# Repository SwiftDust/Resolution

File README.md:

## Resolution

In this repository, I am documenting my progress of learning two new skills: hardware design and CAD. I will hopefully use these in the future to make some really cool projects!

This is made possible by Hack Club's Resolution, a program for teenagers 13-18 years old to learn new skills and earn prizes.

### How it works

I am following the pathways "Hardware" and "Design". These are divided into different weeks: week 1-8. The pathways and weeks have their separate folders with a README to show what the projects are and how I did it, and the project files.

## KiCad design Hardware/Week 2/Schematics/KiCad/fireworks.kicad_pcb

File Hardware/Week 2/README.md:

# Fireworks

This is a fireworks PCB. I made this because starting 2026, fireworks are forbidden on New Years Eve in The Netherlands. Fireworks are always a huge tradition for my family and for our people in general, and I made a little 'fake' firework simulation to make up for it.

## Simulation

The LEDs are all connected to a 5V power source, which routes through 1k capacitors to the LEDs. Between the LEDs and the capacitors are transistors, whose outputs are fed into each other. In between the LEDs are capacitors, which constantly charge and discharge due to the constant change in voltage. This creates a sequencing effect in each of the LED series. They are connected in groups of three.

[Link to schematic](https://is.gd/zdDuyj)

## Schematic

## PCB

---

Much thanks to Rudy (@Outdatedcandy82), for staying super patient and helping me wherever he could!

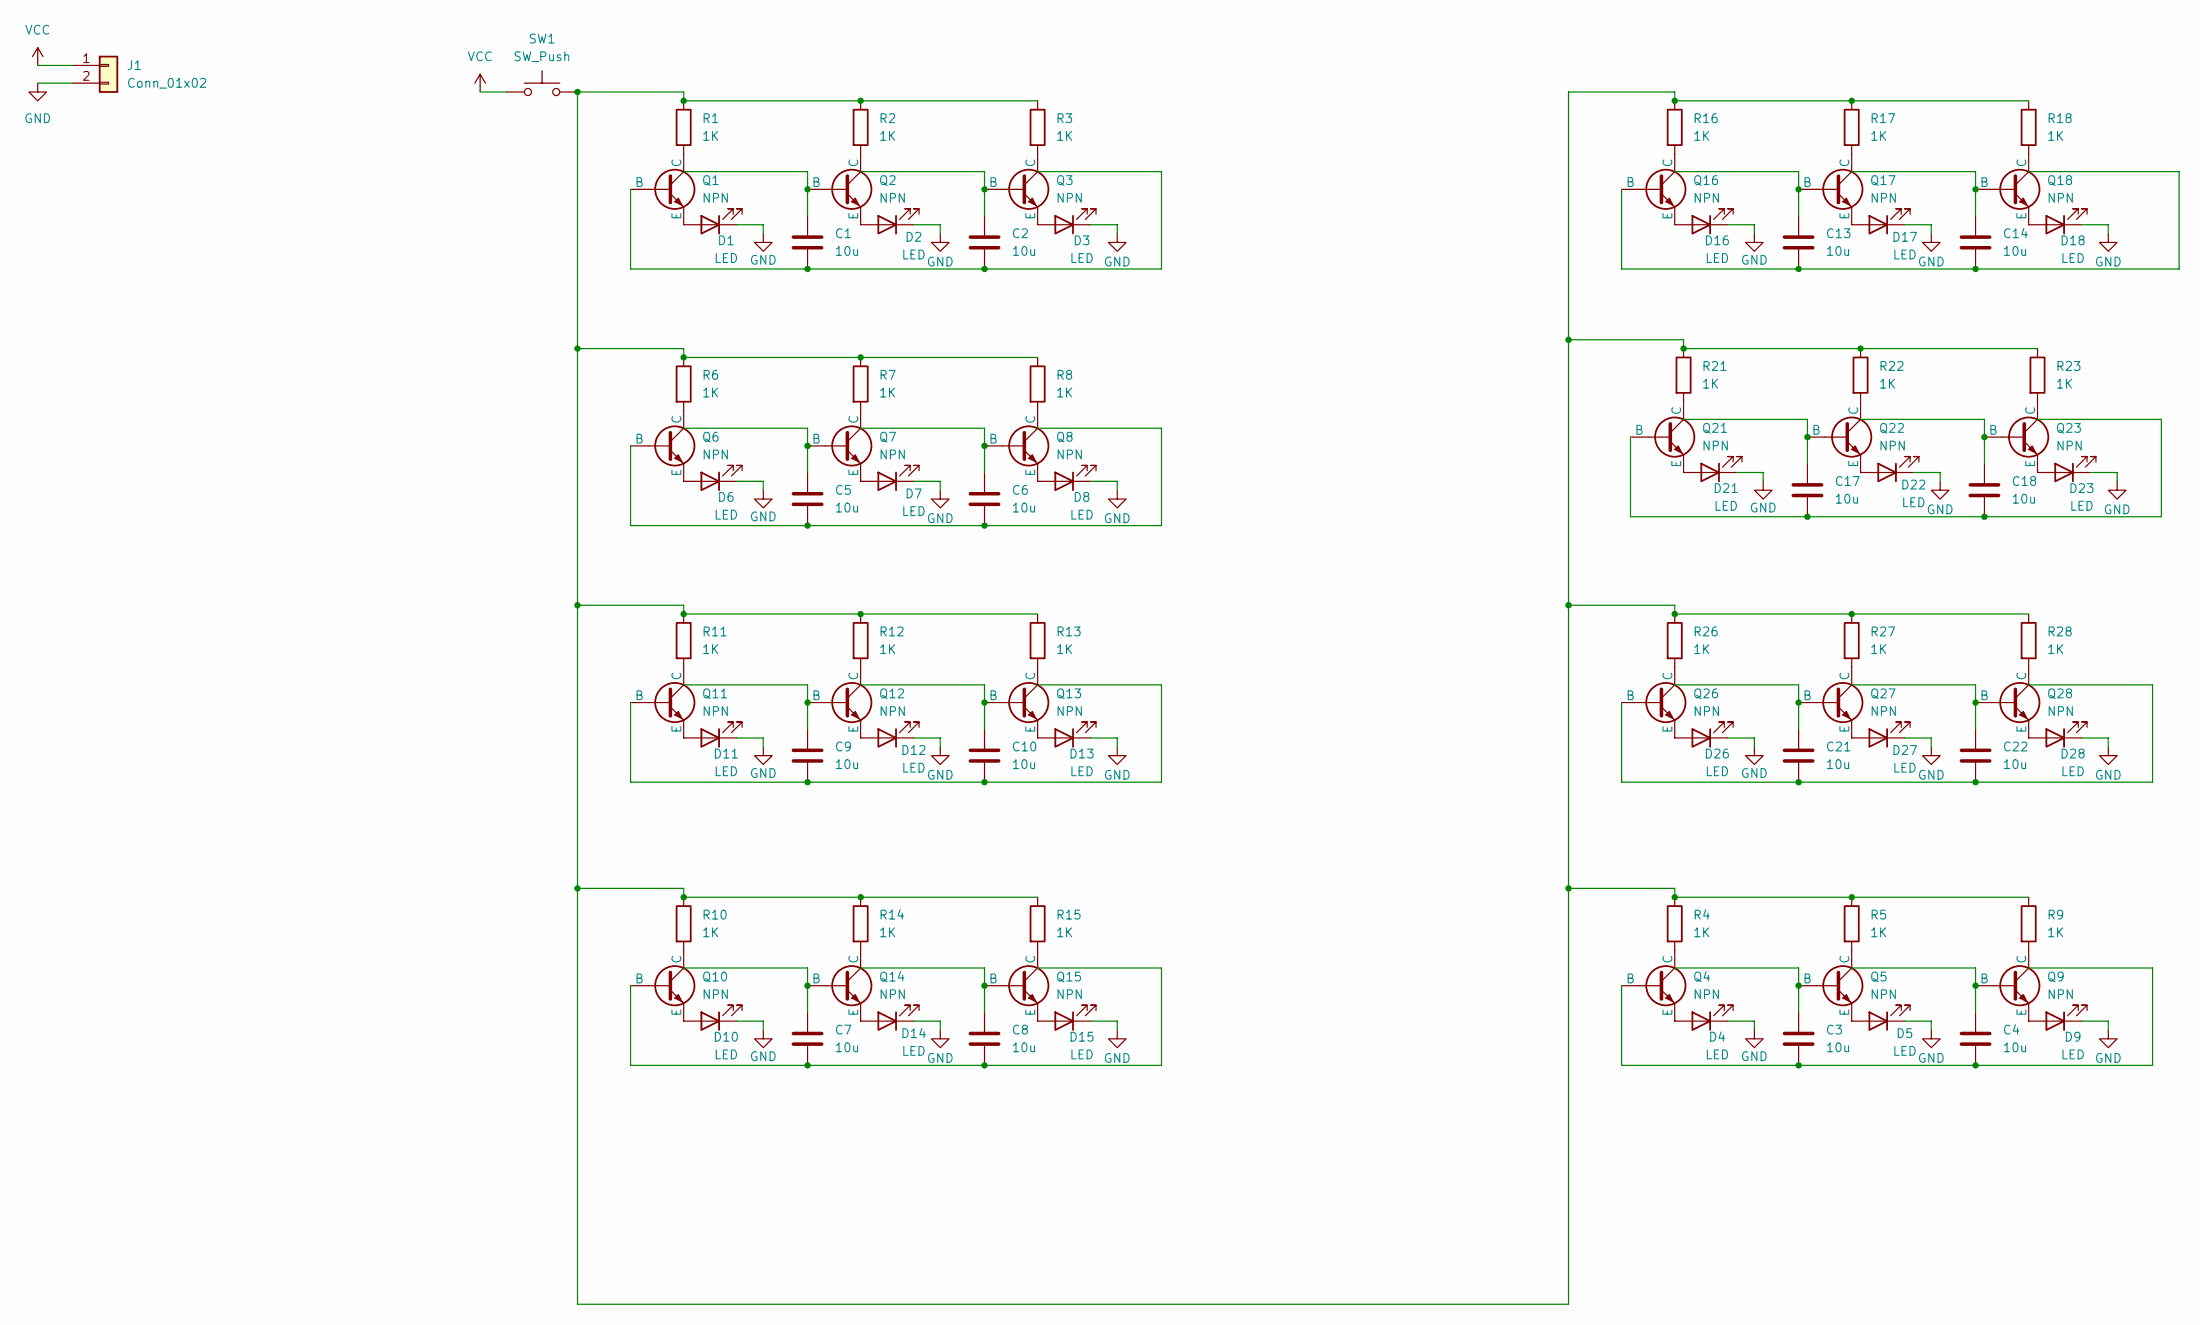
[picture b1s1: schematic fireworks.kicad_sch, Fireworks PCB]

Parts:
C1, C2, C3, C4, C5, C6, C7, C8, C9, C10, C13, C14, C17, C18, C21, C22: 10u; C_Disc_D5.0mm_W2.5mm_P5.00mm
D1, D2, D3, D4, D5, D6, D7, D8, D9, D10, D11, D12, D13, D14, D15, D16, D17, D18, D21, D22, D23, D26, D27, D28: LED; LED_D5.0mm
J1: Conn_01x02; PinHeader_1x02_P2.54mm_Vertical
Q1, Q2, Q3, Q4, Q5, Q6, Q7, Q8, Q9, Q10, Q11, Q12, Q13, Q14, Q15, Q16, Q17, Q18, Q21, Q22, Q23, Q26, Q27, Q28: NPN; TO-92L_Inline_Wide
R1, R2, R3, R4, R5, R6, R7, R8, R9, R10, R11, R12, R13, R14, R15, R16, R17, R18, R21, R22, R23, R26, R27, R28: 1K; R_Axial_DIN0204_L3.6mm_D1.6mm_P7.62mm_Horizontal
SW1: SW_Push; SW_PUSH_6mm

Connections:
GND: D1.1 (K), D2.1 (K), D3.1 (K), D4.1 (K), D5.1 (K), D6.1 (K), D7.1 (K), D8.1 (K), D9.1 (K), D10.1 (K), D11.1 (K), D12.1 (K), D13.1 (K), D14.1 (K), D15.1 (K), D16.1 (K), D17.1 (K), D18.1 (K), D21.1 (K), D22.1 (K), D23.1 (K), D26.1 (K), D27.1 (K), D28.1 (K), J1.2
unnamed: D1.2 (A), Q1.3 (E)
unnamed: D2.2 (A), Q2.3 (E)
unnamed: D3.2 (A), Q3.3 (E)
unnamed: D4.2 (A), Q4.3 (E)
unnamed: D5.2 (A), Q5.3 (E)
unnamed: D6.2 (A), Q6.3 (E)
unnamed: D7.2 (A), Q7.3 (E)
unnamed: D8.2 (A), Q8.3 (E)
unnamed: D9.2 (A), Q9.3 (E)
unnamed: D10.2 (A), Q10.3 (E)
unnamed: D11.2 (A), Q11.3 (E)
unnamed: D12.2 (A), Q12.3 (E)
unnamed: D13.2 (A), Q13.3 (E)
unnamed: D14.2 (A), Q14.3 (E)
unnamed: D15.2 (A), Q15.3 (E)
unnamed: D16.2 (A), Q16.3 (E)
unnamed: D17.2 (A), Q17.3 (E)
unnamed: D18.2 (A), Q18.3 (E)
unnamed: D21.2 (A), Q21.3 (E)
unnamed: D22.2 (A), Q22.3 (E)
unnamed: D23.2 (A), Q23.3 (E)
unnamed: D26.2 (A), Q26.3 (E)
unnamed: D27.2 (A), Q27.3 (E)
unnamed: D28.2 (A), Q28.3 (E)
unnamed: C1.2, C2.2, Q1.2 (B)
unnamed: Q1.1 (C), R1.2
unnamed: C1.1, Q2.2 (B)
unnamed: Q2.1 (C), R2.2
unnamed: C2.1, Q3.2 (B)
unnamed: Q3.1 (C), R3.2
unnamed: C3.2, C4.2, Q4.2 (B)
unnamed: Q4.1 (C), R4.2
unnamed: C3.1, Q5.2 (B)
unnamed: Q5.1 (C), R5.2
unnamed: C5.2, C6.2, Q6.2 (B)
unnamed: Q6.1 (C), R6.2
unnamed: C5.1, Q7.2 (B)
unnamed: Q7.1 (C), R7.2
unnamed: C6.1, Q8.2 (B)
unnamed: Q8.1 (C), R8.2
unnamed: C4.1, Q9.2 (B)
unnamed: Q9.1 (C), R9.2
unnamed: C7.2, C8.2, Q10.2 (B)
unnamed: Q10.1 (C), R10.2
unnamed: C9.2, C10.2, Q11.2 (B)
unnamed: Q11.1 (C), R11.2
unnamed: C9.1, Q12.2 (B)
unnamed: Q12.1 (C), R12.2
unnamed: C10.1, Q13.2 (B)
unnamed: Q13.1 (C), R13.2
unnamed: C7.1, Q14.2 (B)
unnamed: Q14.1 (C), R14.2
unnamed: C8.1, Q15.2 (B)
unnamed: Q15.1 (C), R15.2
unnamed: C13.2, C14.2, Q16.2 (B)
unnamed: Q16.1 (C), R16.2
unnamed: C13.1, Q17.2 (B)
unnamed: Q17.1 (C), R17.2
unnamed: C14.1, Q18.2 (B)
unnamed: Q18.1 (C), R18.2
unnamed: C17.2, C18.2, Q21.2 (B)
unnamed: Q21.1 (C), R21.2
unnamed: C17.1, Q22.2 (B)
unnamed: Q22.1 (C), R22.2
unnamed: C18.1, Q23.2 (B)
unnamed: Q23.1 (C), R23.2
unnamed: C21.2, C22.2, Q26.2 (B)
unnamed: Q26.1 (C), R26.2
unnamed: C21.1, Q27.2 (B)
unnamed: Q27.1 (C), R27.2
unnamed: C22.1, Q28.2 (B)
unnamed: Q28.1 (C), R28.2
unnamed: R1.1, R2.1, R3.1, R4.1, R5.1, R6.1, R7.1, R8.1, R9.1, R10.1, R11.1, R12.1, R13.1, R14.1, R15.1, R16.1, R17.1, R18.1, R21.1, R22.1, R23.1, R26.1, R27.1, R28.1, SW1.2
VCC: J1.1, SW1.1

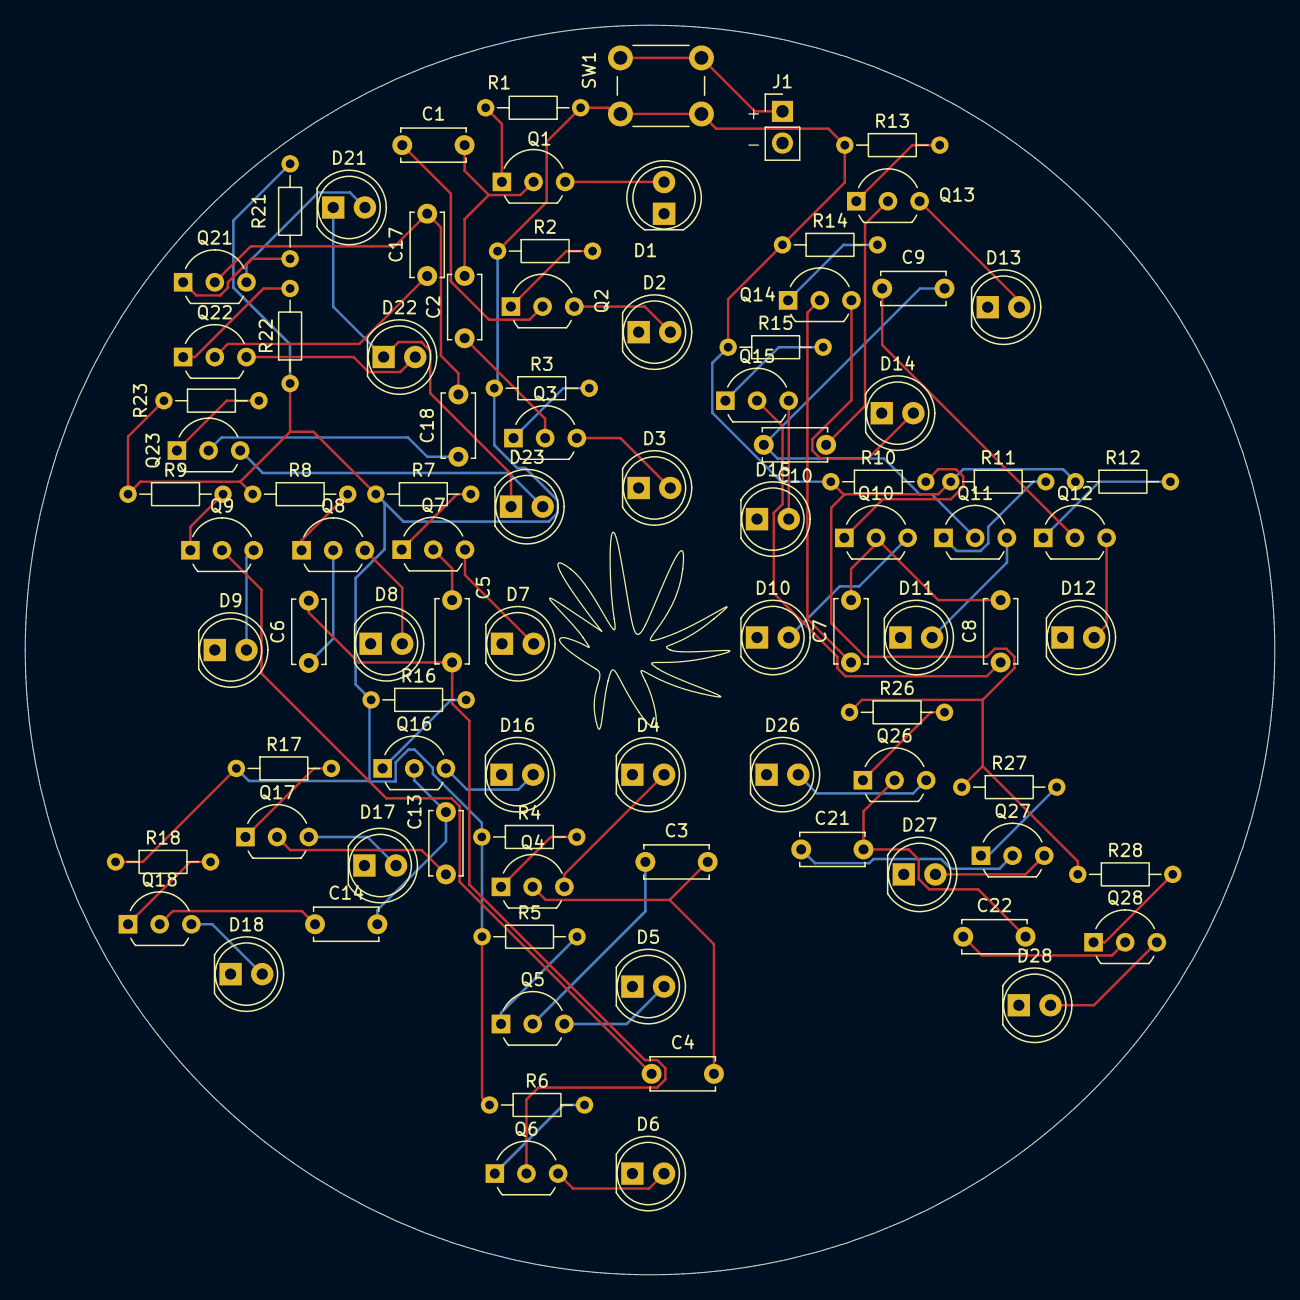
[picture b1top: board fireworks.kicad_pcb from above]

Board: 2 copper layers, 100.2 x 100.2 mm, 90 parts (0 on the bottom side), 75 nets.

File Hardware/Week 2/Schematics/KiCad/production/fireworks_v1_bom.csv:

Designator,Footprint,Quantity,Value,LCSC Part #
"C1, C10, C13, C14, C17, C18, C2, C21, C22, C3, C4, C5, C6, C7, C8, C9",PinHeader_1x02_P2.54mm_Vertical,16,10u,
"D1, D10, D11, D12, D13, D14, D15, D16, D17, D18, D2, D21, D22, D23, D26, D27, D28, D3, D4, D5, D6, D7, D8, D9",LED_D5.0mm,24,LED,
J1,PinHeader_1x02_P2.54mm_Vertical,1,Conn_01x02,
"Q1, Q10, Q11, Q12, Q13, Q14, Q15, Q16, Q17, Q18, Q2, Q21, Q22, Q23, Q26, Q27, Q28, Q3, Q4, Q5, Q6, Q7, Q8, Q9",TO-92L_Inline_Wide,24,NPN,
"R1, R10, R11, R12, R13, R14, R15, R16, R17, R18, R2, R21, R22, R23, R26, R27, R28, R3, R4, R5, R6, R7, R8, R9",R_Axial_DIN0204_L3.6mm_D1.6mm_P7.62mm_Horizontal,24,1K,
SW1,SW_PUSH_6mm,1,SW_Push,

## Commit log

2026-03-10 Add video and explanation to README of week one
2026-03-14 Add Caps Lock keycap of CAD Design Week 1
2026-03-14 Add image for Caps Lock key design in README
2026-03-15 Upload space bar key
2026-03-15 Add Tab key
2026-03-15 Add screenshots for the keycaps
2026-03-15 Revise README.md with updated keycap images
    Updated image links for keycaps and added new sections for Spacebar and Tab keys.
2026-03-18 Add the Falstad simulation for the LED sequencer
2026-03-19 Add switch and schematic
2026-03-19 Finish the schematic
2026-03-23 Add fabrication files and finish routing
2026-03-23 Add the documentation for week 2
2026-04-04 Resolve DRC errors
2026-06-28 Correct capacitor footprint
